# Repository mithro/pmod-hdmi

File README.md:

# pmod-hdmi-XX

 * See the [TX branch](https://github.com/mithro/pmod-hdmi/tree/tx) for a HDMI transmitter based around a PTN3363.
 * See the [RX branch](https://github.com/mithro/pmod-hdmi/tree/rx) for a HDMI receiver based around a AD8195.

## License

The board template for KiCad is licensed under a Creative Commons
Attribution 4.0 International License.

You should have received a copy of the license along with this
work.  If not, see <http://creativecommons.org/licenses/by/4.0/>.

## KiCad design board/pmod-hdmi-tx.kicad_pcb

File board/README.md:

# Length Matching

 * HDMI_PMOD2CAP
  - 0.4872" (12.37488 mm)
  - 10mil intra pair
  - 1mil inter pair

 * HDMI_CAP2IC
  - 10mil intra pair
  - 1mil inter pair

 * HDMI_I22PORT
  - 15mil intra pair
  - 1mil inter pair

# Board Manufacturing

 *  5mil (0.127mm) trace width
 *  5mil (0.127mm) trace clearance

 * 12 mil (0.3048mm) drill size
 *  6 mil (0.1524mm) annular ring
 * 24 mil (0.6096mm) via size (6mil+12mil+6mil)

 *  6 mil (0.1524) silkscreen width

This can be meet by;
 * [Hackvana by requesting the 5mil option](https://docs.google.com/document/d/1p6FH25ltGpzJQ5_8fbflDukqEKghiEcpuhJpngth2Is/edit)
 * [OHS Park's Four Layer Boards](http://docs.oshpark.com/services/)

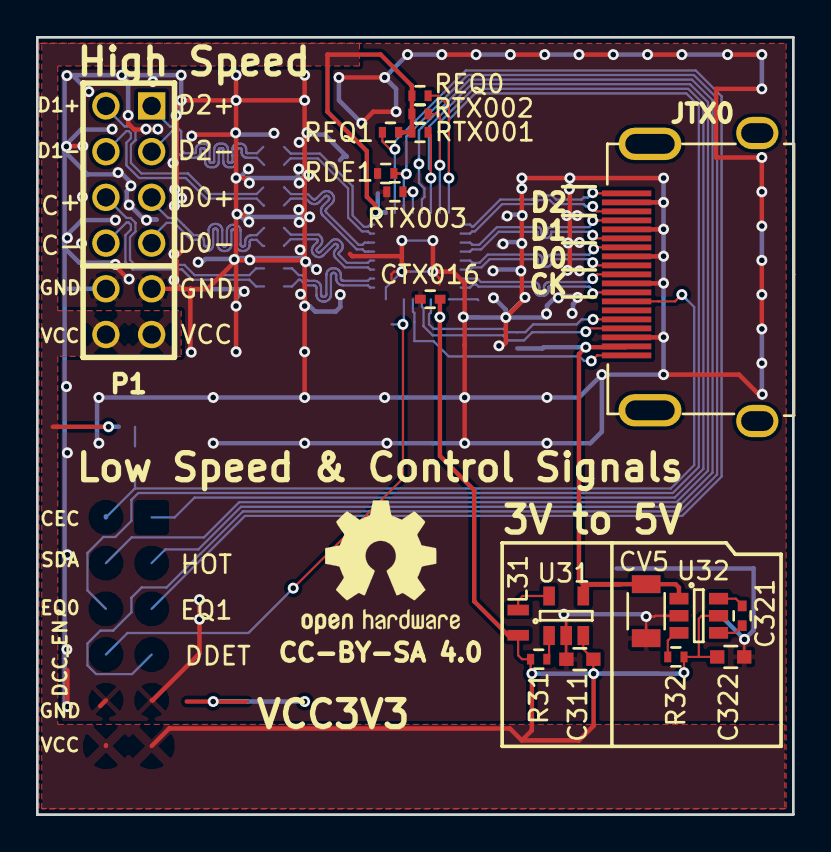
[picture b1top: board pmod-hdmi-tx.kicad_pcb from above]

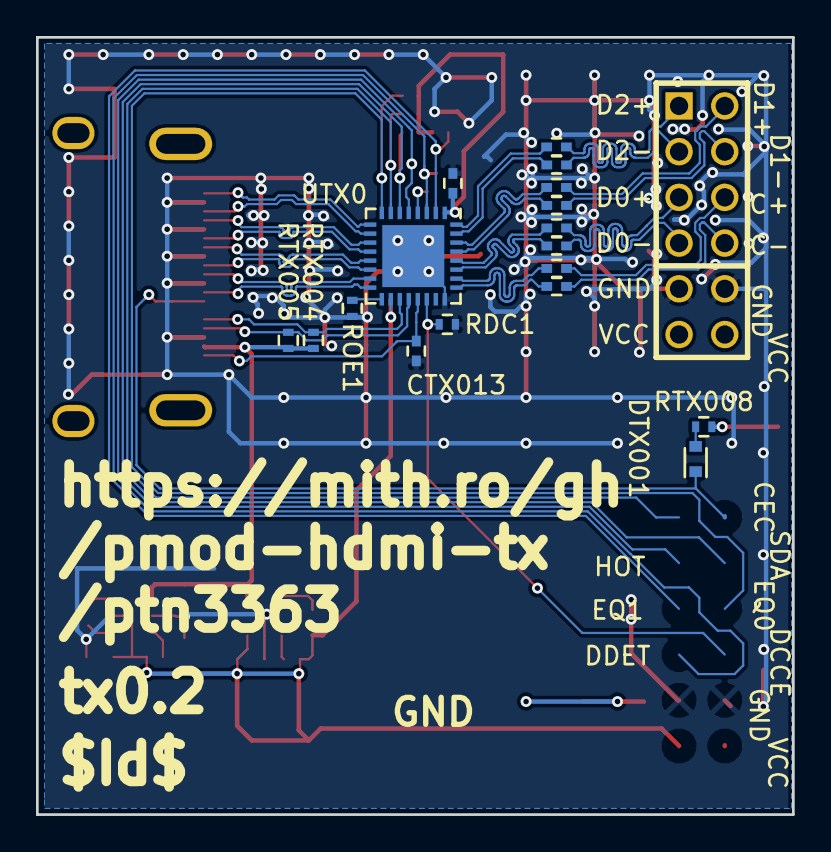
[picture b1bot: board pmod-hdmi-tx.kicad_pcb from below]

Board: 2 copper layers, 42.0 x 43.2 mm, 35 parts (17 on the bottom side), 38 nets.

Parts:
C311: 4.7uF; C_0603
C321: 220n; C_0402
C322: 2.2uF; C_0603
CTX001, CTX002, CTX003, CTX004, CTX005, CTX006, CTX007, CTX008, CTX016, CTX017: 0.1uF; C_0402
CTX013: 10n; C_0402
CV5: 10uF; C_1206
DTX001: D; SOD-523
JTX0: HDMI_OUT; HDMI_TH
L31: 4.7uH; Neosid_Inductor_SM0603CG
P1: PMOD-Device-x2-Type-XHS-Alt; pmod_pin_array_6x2
R31: 4.7k; R_0402
R32: 10k; R_0402
RDC1: 10k; R_0402
RDE1: 10k; R_0402
REQ0, REQ1: 10k; R_0402
ROE1: 10k; R_0402
RTX001, RTX002, RTX004, RTX005: 2k2; R_0402
RTX003: 12k4; R_0402
RTX008: 27K; R_0402
U31: XC9140; SOT-23-5
U32: REG710-DBV; SOT-23-6
UTX0: PTN3363; QFN-32-1EP_5x5mm_Pitch0.5mm

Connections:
/HDMI TX/HDMIA_TX0_CLK+: CTX001.1, UTX0.26
/HDMI TX/HDMIA_TX0_CLK-: CTX002.1, UTX0.25
/HDMI TX/HDMIA_TX0_D0+: CTX003.1, UTX0.28
/HDMI TX/HDMIA_TX0_D0-: CTX004.1, UTX0.27
/HDMI TX/HDMIA_TX0_D1+: CTX005.1, UTX0.30
/HDMI TX/HDMIA_TX0_D1-: CTX006.1, UTX0.29
/HDMI TX/HDMIA_TX0_D2+: CTX007.1, UTX0.32
/HDMI TX/HDMIA_TX0_D2-: CTX008.1, UTX0.31
/HDMI TX/HDMIP_TX0_CLK+: JTX0.10, UTX0.15
/HDMI TX/HDMIP_TX0_CLK-: JTX0.12, UTX0.16
/HDMI TX/HDMIP_TX0_D0+: JTX0.7, UTX0.13
/HDMI TX/HDMIP_TX0_D0-: JTX0.9, UTX0.14
/HDMI TX/HDMIP_TX0_D1+: JTX0.4, UTX0.11
/HDMI TX/HDMIP_TX0_D1-: JTX0.6, UTX0.12
/HDMI TX/HDMIP_TX0_D2+: JTX0.1, UTX0.9
/HDMI TX/HDMIP_TX0_D2-: JTX0.3, UTX0.10
/HDMI TX/HDMIP_TX0_HOT: CTX013.2, JTX0.19, UTX0.21
/HDMI TX/HDMIP_TX0_SCL: JTX0.15, RTX004.2, UTX0.19
/HDMI TX/HDMIP_TX0_SDA: JTX0.16, RTX005.2, UTX0.20
/HDMI_TX0_CEC: DTX001.1, JTX0.13, P1.7
/HDMI_TX0_DCC_EN: P1.10, RDC1.2, UTX0.22
/HDMI_TX0_DDET: P1.4, RDE1.2, UTX0.3
/HDMI_TX0_EQ0: P1.9, REQ0.2, UTX0.8
/HDMI_TX0_EQ1: P1.3, REQ1.2, UTX0.2
/HDMI_TX0_HOT: P1.2, UTX0.5
/HDMI_TX0_SCL: P1.1, RTX002.2, UTX0.7
/HDMI_TX0_SDA: P1.8, RTX001.2, UTX0.6
/~HDMI_TX0_OE: ROE1.2, UTX0.17
GND: C311.2, C322.2, CTX013.1, CTX016.1, CTX017.1, CV5.2, JTX0.2, JTX0.5, JTX0.8, JTX0.11, JTX0.17, P1.5, P1.11, RDC1.1, RDE1.1, ROE1.1, RTX003.2, U31.2, U32.2, UTX0.24, UTX0.33
unnamed: C321.1, U32.6
unnamed: C321.2, U32.4
unnamed: DTX001.2, RTX008.2
unnamed: L31.2, U31.5
unnamed: R31.1, U31.1
unnamed: R32.1, U32.3
unnamed: RTX003.1, UTX0.4
TX05V0: CV5.1, JTX0.18, RTX004.1, RTX005.1, U31.4, U32.1
VCC3V3: C311.1, C322.1, CTX016.2, CTX017.2, L31.1, P1.6, P1.12, R31.2, R32.2, REQ0.1, REQ1.1, RTX001.1, RTX002.1, RTX008.1, U31.3, U32.5, UTX0.1, UTX0.18

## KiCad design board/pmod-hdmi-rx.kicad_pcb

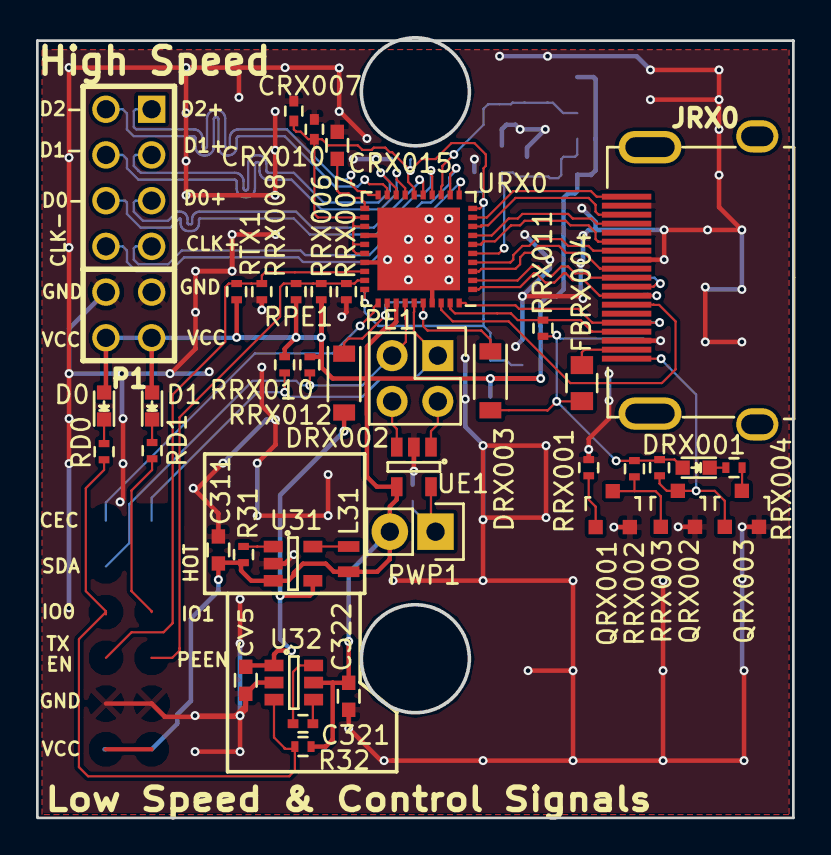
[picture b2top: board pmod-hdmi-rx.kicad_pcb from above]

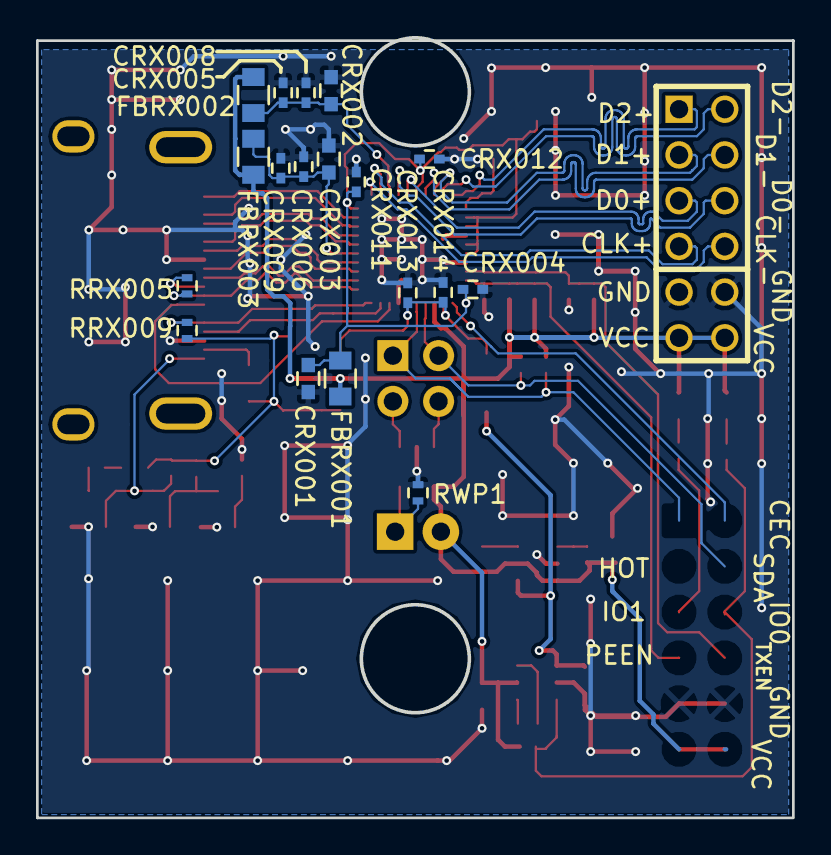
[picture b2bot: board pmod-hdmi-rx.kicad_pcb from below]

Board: 2 copper layers, 42.0 x 43.3 mm, 59 parts (18 on the bottom side), 43 nets.

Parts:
C311: 4.7uF; C_0603
C321: 220n; C_0402
C322: 2.2uF; C_0603
CRX001, CRX002, CRX003, CRX015: 10uF; C_0603
CRX004, CRX005, CRX006, CRX007, CRX010: 0.1uF; C_0402
CRX008, CRX009, CRX011, CRX012, CRX014: 10nF; C_0402
CRX013: 0.1nF; C_0402
CV5: 10uF; C_0603
D0, D1: LED; LED_0603
DRX001: LED; LED_0603
DRX002, DRX003: D; SOD-123
FBRX001, FBRX002, FBRX003, FBRX004: FILTER; C_0805
JRX0: HDMI_IN; HDMI_TH
L31: 4.7uH; Neosid_Inductor_SM0603CG
P1: PMOD-CONN_6X2; pmod_pin_array_6x2
PE1: CONN_02X02; Pin_Header_Straight_2x02
PWP1: CONN_02X01; Pin_Header_Straight_1x02
QRX001, QRX002, QRX003: FDV301N; SOT-23
R31: 4.7k; R_0402
R32: 10k; R_0402
RD0, RD1: 100; R_0402
RPE1: 10k; R_0402
RRX001, RRX002, RRX006, RRX007, RRX008: 100K; R_0402
RRX003, RRX010, RRX012: 1K; R_0402
RRX004: 560R; R_0402
RRX005: 2K; R_0402
RRX009, RRX011: 47K; R_0402
RTX1: 10k; R_0402
RWP1: 10k; R_0402
U31: XC9140; SOT-23-5
U32: REG710-DBV; SOT-23-6
UE1: 24AA01/24LC01B; SOT-23-5
URX0: AD8195; QFN-40-1EP_6x6mm_Pitch0.5mm

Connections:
/EEPROM_SCL: PE1.2, UE1.1
/EEPROM_SDA: PE1.4, UE1.3
/HDMI RX/AVCC3V3: CRX001.1, CRX004.1, CRX007.1, CRX010.1, CRX011.1, CRX012.1, FBRX001.2, URX0.10, URX0.16, URX0.22, URX0.23, URX0.25, URX0.26, URX0.30
/HDMI RX/HDMIP_RX0_CEC: JRX0.13, URX0.38
/HDMI RX/HDMIP_RX0_CLK+: JRX0.10, URX0.2
/HDMI RX/HDMIP_RX0_CLK-: JRX0.12, RRX005.1, URX0.1
/HDMI RX/HDMIP_RX0_D0+: JRX0.7, URX0.4
/HDMI RX/HDMIP_RX0_D0-: JRX0.9, URX0.3
/HDMI RX/HDMIP_RX0_D1+: JRX0.4, URX0.7
/HDMI RX/HDMIP_RX0_D1-: JRX0.6, URX0.6
/HDMI RX/HDMIP_RX0_D2+: JRX0.1, URX0.9
/HDMI RX/HDMIP_RX0_D2-: JRX0.3, URX0.8
/HDMI RX/HDMIP_RX0_HOT: JRX0.19, QRX002.3, QRX003.1, RRX003.1
/HDMI RX/HDMIP_RX0_SCL: JRX0.15, RRX009.1, URX0.40
/HDMI RX/HDMIP_RX0_SDA: JRX0.16, RRX011.1, URX0.39
/HDMI RX/HDMI_RX0_HOT: P1.2, QRX001.1, RRX001.2
/HDMI RX/VCC5V0_RX0: DRX001.2, DRX003.2, FBRX004.2, RRX002.2, RRX003.2, RRX009.2, RRX011.2
/HDMI RX/VTTI3V3: CRX003.1, CRX006.1, CRX009.1, FBRX003.2, URX0.5
/HDMI RX/VTTO3V3: CRX002.1, CRX005.1, CRX008.1, FBRX002.2, URX0.13
/HDMI_RX0_CEC: P1.7, URX0.31
/HDMI_RX0_IO0: P1.9, R32.1, RD0.2, U32.3
/HDMI_RX0_IO1: P1.3, RD1.2
/HDMI_RX0_PEEN: P1.4, RPE1.2, RRX006.2, RRX007.1, URX0.29
/HDMI_RX0_SCL: P1.1, PE1.1, RRX010.1, URX0.35
/HDMI_RX0_SDA: P1.8, PE1.3, RRX012.1, URX0.34
/HDMI_RX0_TXEN: P1.10, RRX008.1, RTX1.2, URX0.28
GND: C311.2, C322.2, CRX001.2, CRX002.2, CRX003.2, CRX004.2, CRX005.2, CRX006.2, CRX007.2, CRX008.2, CRX009.2, CRX010.2, CRX011.2, CRX012.2, CRX013.2, CRX014.2, CRX015.2, CV5.2, JRX0.2, JRX0.5, JRX0.8, JRX0.17, P1.5, P1.11, QRX001.2, QRX002.2, QRX003.2, RRX001.1, RRX007.2, RRX008.2, RWP1.2, U31.2, U32.2, UE1.2, URX0.24, URX0.27, URX0.37, URX0.41
unnamed: C321.1, U32.6
unnamed: C321.2, U32.4
unnamed: CRX013.1, CRX014.1, DRX002.1, DRX003.1, URX0.32, URX0.36
unnamed: CRX015.1, URX0.21
unnamed: D0.1, RD0.1
unnamed: D1.1, RD1.1
unnamed: DRX001.1, RRX004.2
unnamed: FBRX004.1, JRX0.18
unnamed: JRX0.11, RRX005.2
unnamed: L31.2, U31.5
unnamed: PWP1.1, RWP1.1, UE1.5
unnamed: QRX001.3, QRX002.1, RRX002.1
unnamed: QRX003.3, RRX004.1
unnamed: R31.1, U31.1
VCC3V3: C311.1, C322.1, D0.2, D1.2, FBRX001.1, FBRX002.1, FBRX003.1, L31.1, P1.6, P1.12, PWP1.2, R31.2, R32.2, RPE1.1, RRX006.1, RRX010.2, RRX012.2, RTX1.1, U31.3, U32.5, UE1.4, URX0.33
VCC5V0: CV5.1, DRX002.2, U31.4, U32.1

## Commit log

2016-10-16 Updating README.
2016-10-16 Adding CC-BY-SA 4.0 license.
2016-10-16 Adding submodules.
2016-10-16 24A EEPROM from TOFE library.
2016-10-16 Adding XC9140 3V3 to 5V voltage booster.
2016-10-16 Adding schematic.
2016-10-16 Adding script to pull the HDMI TX template.
2016-10-16 Adding HDMI input from template.
2016-10-16 Updating template script.
2016-10-16 Updating from template.
2016-10-16 Update from template.
2016-10-16 Mostly working schematic.
2016-10-16 Annotate schematic.
2016-10-16 Adding footprints.
2016-10-16 Assigning footprints.
2016-10-16 Update from tempaltes.
2016-10-16 Setting up schematic.
2016-10-16 Update from the template.
2016-10-16 Updating the PCB a little.
2016-10-16 Starting the RX version.
2016-10-16 Rewriting for RX.
2016-10-16 Moving the templated.
2016-10-16 Getting RX wired up.
2016-10-16 Adding missing libraries.
2016-10-16 s/tx/rx/
2016-10-16 Slowly getting the RX version working.
2016-10-16 Updating the PCB.
2016-10-16 Fixing the formatting.
2016-10-27 First version from Phyllis.
2016-11-03 Second version from Phyllis.
2016-11-10 Update from templates + s/HPD/HOT/ + s/HPA/HOT/
2016-11-10 Updating pmod library.
2016-11-10 Update from templates.
2016-11-10 Changing how the high speed signals are routed.
2016-11-10 Reorganising the high speed signals.
2016-11-10 Fixing the PCB now.
2016-11-15 Slowly working on getting first working from templates.
2016-11-19 Working on making the high speed lines better.
2016-11-19 Reworking stuff.
2016-11-23 Adding CE for XC9140 part.
2016-11-27 Starting to get length matching right...
2016-11-27 First group matches length.
2016-11-27 Lots of small changes...
2016-11-27 Everything matches.
2016-11-27 Fixing silkscreen.
2016-11-27 Small fixes.
2016-11-27 Adding a release script.
2016-11-27 Fiddling with the silkscreen.
2016-11-27 Playing with release script.
2016-11-27 Tweaking embedded version.
2016-11-27 Trying to get the Id working.
2016-11-27 Tweaking a track.
2016-11-28 Working on updating from templates better.
2016-12-10 Starting on length matching.
2016-12-10 Temp commit.
2017-07-15 Adding GND/VCC open area.
2017-07-15 Fiddling with the silkscreen more.
2017-07-15 Fixing the high speed labels.
2017-07-15 Bumping version to tx0.1
2017-07-27 Clearance of 0.1269mm
2017-07-27 Setting clearance correctly.
2017-07-27 Fixing the via sizes.
2017-07-27 Fixing the via DRC violations.
2017-07-28 More fixes.
2018-04-05 A bunch of cleanup, see detailed comment below.
    * Reorganized value labels for a better manual placement plan.
    * Replaced manually created dimensions using KiCad dimension object.
    * Removed dimensions that were not anchored to anything obviously
    useful. I assume they are cutandpasta remains.
    * Removed floating items on the Cmts.User layer.
    * Fab notes merged into a single object. There is no need to write the
2018-04-05 Value position adjustment on bottom layer for placement plan.
2018-04-05 Adjusted value positions for top side manual placement plan.
